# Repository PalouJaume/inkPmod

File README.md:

# __inkPmod__

# Welcome! 👋

Hi there! This repo documents a personal project where I extended the functionality of the Pynq Z2 board by adding support for an E-Ink display from Adafruit. Since none of the available Pmod modules quite met my needs, I decided to roll up my sleeves and design a custom Pmod board using KiCad.

To make the integration seamless, I also created a custom IP block to handle communication between the Pynq board and the E-Ink display. On top of that, I developed a simple C API, allowing control of the display in both bare-metal applications and on a lightweight Linux distribution.

## 🎯 Objective 

Aside from playing around with E-Ink displays and FPC connectors, this project is also a chance for me to sharpen my PCB design skills and learn a few new tricks along the way. Here's what I'm focusing on:

- Deepening my understanding of PCB layout best practices
- Exploring practical applications of stitching vias
- Working through hands-on design challenges with a real-world component

### 📚 Learning Resources

To guide the process, I'm referencing a few great resources:

- 📘 [PCB Design Tutorial (Stanford)](https://www.scs.stanford.edu/~zyedidia/docs/pcb/pcb_tutorial.pdf)
- 📺 [2-Layer PCB Design Tips – Phil's Lab #137 (YouTube)](https://www.youtube.com/watch?v=M6_an34wQJk&t=85s)
- 🧠 [Everything You Need to Know About Stitching Vias (Altium)](https://resources.altium.com/p/everything-you-need-know-about-stitching-vias)

## 🔧 Hardware Design & Schematics

The core of this project revolves around the 2.13" Flexible Monochrome E-Ink Display from Adafruit:

[2.13" Flexible eInk Display – 212x104 Monochrome](https://www.adafruit.com/product/4243)

To design the custom Pmod, I based my schematics on the reference circuit provided in the official datasheet:

📄 [Display Datasheet (PDF)](https://cdn-shop.adafruit.com/product-files/4243/4243_datahseet_GDEW0213I5F_V1.1_Specification__1_.pdf)

Before diving into the layout, I identified the key components and signal requirements based on this reference. My focus was on building a compact and reliable interface that would be easy to integrate with the Pynq Z2.

## 🛠️ Features (WIP)
This project is still a work in progress, but here’s a sneak peek at what I’ve implemented or planned:

- 🔄 Custom Pmod-compatible board in KiCad

- 🔜 Basic working schematic & layout

- 🔜 Photos of the board being tested

- 🔜 Custom IP block for display communication

- 🔜 C API for easy control (bare-metal & Linux)

## 💬 Why I'm Sharing This
I’m sharing this not just to document my own journey, but in hopes it might help others who are exploring similar ideas—or inspire someone to try a custom Pmod project of their own!

If you have feedback, suggestions, or just want to geek out about FPC connectors and Pynq projects, feel free to open an issue or drop a message. 😊

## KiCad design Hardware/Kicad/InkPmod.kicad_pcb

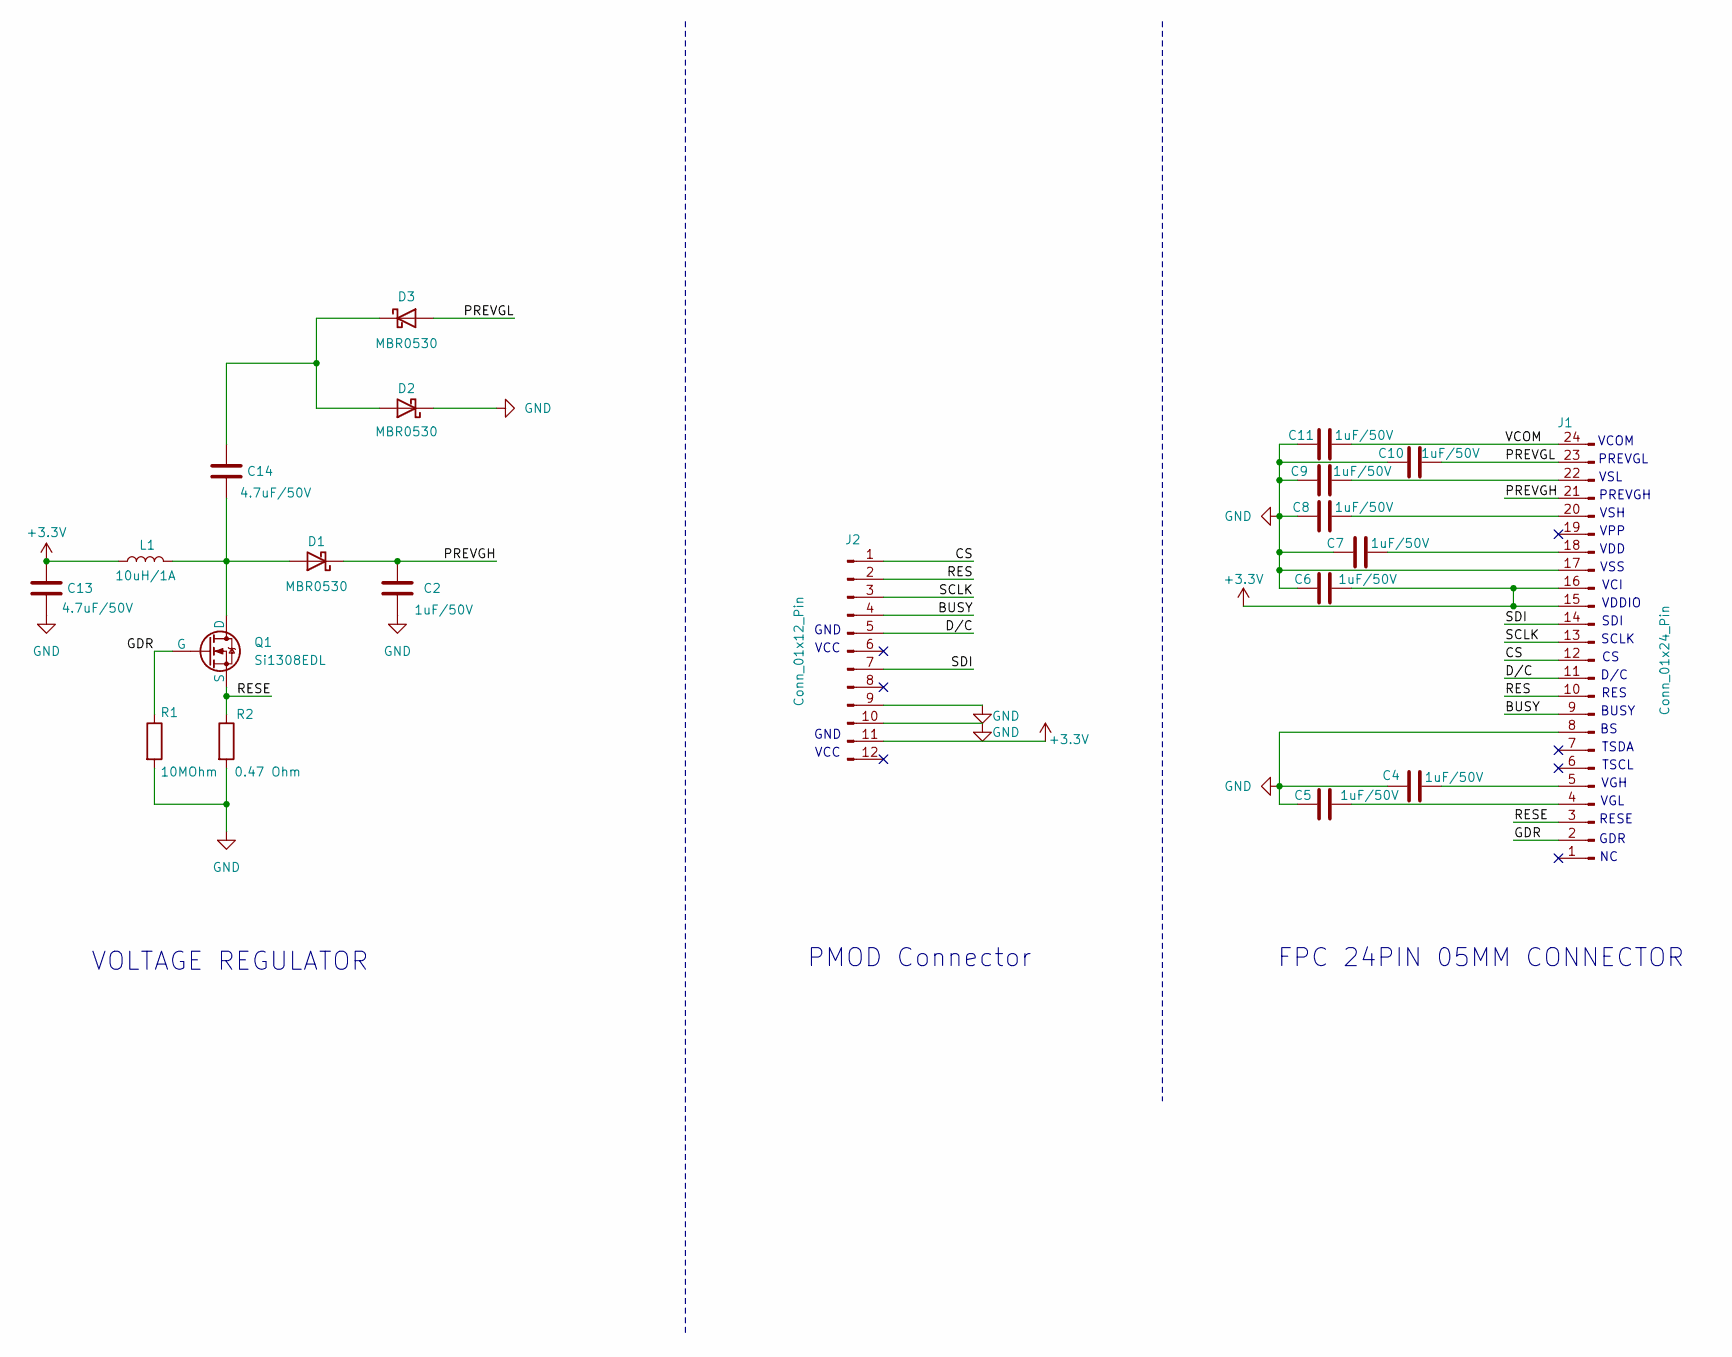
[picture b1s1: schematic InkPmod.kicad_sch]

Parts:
C2, C4, C5, C6, C7, C8, C9, C10, C11: 1uF/50V; C_1206_3216Metric_Pad1.33x1.80mm_HandSolder
C13, C14: 4.7uF/50V; C_1206_3216Metric_Pad1.33x1.80mm_HandSolder
D1, D2, D3: MBR0530; D_SOD-123
J1: Conn_01x24_Pin; Molex_FPC_24_05MM
J2: Conn_01x12_Pin; PinHeader_2x06_P1.27mm_Vertical
L1: 10uH/1A; IDCP2218-01
Q1: Si1308EDL; SOT-323_SC-70_Handsoldering
R1: 10MOhm; R_1206_3216Metric_Pad1.30x1.75mm_HandSolder
R2: 0.47 Ohm; R_1206_3216Metric_Pad1.30x1.75mm_HandSolder

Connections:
+3.3V: C6.2, C13.1, J1.15, J1.16, J2.11, L1.1
/BUSY: J1.9, J2.4
/CS: J1.12, J2.1
/D/C: J1.11, J2.5
/GDR: J1.2, Q1.2 (G), R1.1
/PREVGH: C2.1, D1.1 (K), J1.21
/PREVGL: C10.2, D3.2 (A), J1.23
/RES: J1.10, J2.2
/RESE: J1.3, Q1.3 (S), R2.1
/SCLK: J1.13, J2.3
/SDI: J1.14, J2.7
/VCOM: C11.2, J1.24
GND: C2.2, C4.1, C5.1, C6.1, C7.1, C8.1, C9.1, C10.1, C11.1, C13.2, D2.1 (K), J1.8, J1.17, J2.9, J2.10, R1.2, R2.2; also elsewhere on the board
unnamed: C14.2, D1.2 (A), L1.2, Q1.1 (D)
unnamed: C14.1, D2.2 (A), D3.1 (K)
unnamed: C5.2, J1.4
unnamed: C4.2, J1.5
unnamed: C7.2, J1.18
unnamed: C8.2, J1.20
unnamed: C9.2, J1.22

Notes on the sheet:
GND
FPC 24PIN 05MM CONNECTOR
RESE
VDDIO
TSDA
SDI
TSCL
VSS
VCI
PMOD Connector
VDD
VCOM
RES
VGL
VOLTAGE REGULATOR
D/C
BUSY
VPP
VCC
VSL
VGH
PREVGL
PREVGH
SCLK
GDR
VSH

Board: 2 copper layers, 21 parts (1 on the bottom side), 20 nets, no tracks yet.

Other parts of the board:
C12: 1uF/50V; C_1206_3216Metric_Pad1.33x1.80mm_HandSolder

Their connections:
GND: C12.1; also elsewhere on the board

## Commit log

2025-04-12 Sets basic layout of the proyect
2025-04-19 Add guidelines of the project
2025-04-24 Add basic reasearch previous Hardware Design
2025-04-24 Corrects mismatch README file
